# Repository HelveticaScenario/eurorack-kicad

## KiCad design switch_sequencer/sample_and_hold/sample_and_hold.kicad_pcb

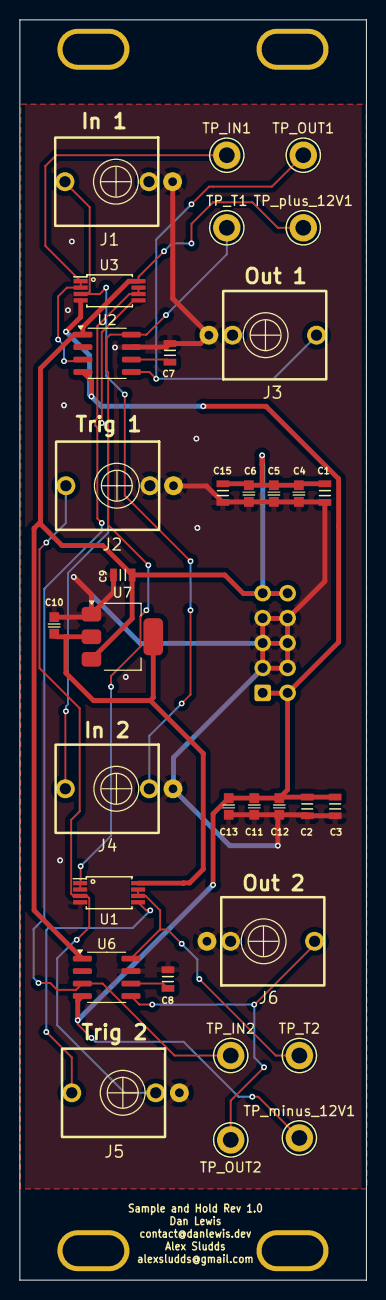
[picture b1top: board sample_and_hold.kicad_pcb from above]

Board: 2 copper layers, 35.3 x 128.5 mm, 38 parts (1 on the bottom side), 16 nets.

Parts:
C1, C2, C3, C15: 22uF_0603_16V; C_0805
C4, C5, C6, C11, C12, C13: 100nF_0603_16V; C_0603
C7, C8, C9: 0.1uF_0805_50V; C_0805
C10: 10uF_0603_10V; C_0603
H1, H2, H3, H4: MountingHole; Faceplate_Rail_Mount_Slot_Plated
J1, J2, J3, J4, J5, J6: 3.5mm_Mono_Switched_sm; EighthInch_PJ398SM
J7: Eurorack_Power_10pin_Shrouded; Pins_2x05_2.54mm_TH_EurorackPower_Shrouded
TP_IN1, TP_IN2: TestPoint; TestPoint_Keystone_5005-5009_Compact
TP_OUT1, TP_OUT2: TestPoint; TestPoint_Keystone_5005-5009_Compact
TP_T1, TP_T2: TestPoint; TestPoint_Keystone_5005-5009_Compact
TP_minus_12V1: TestPoint; TestPoint_Keystone_5005-5009_Compact
TP_plus_12V1: TestPoint; TestPoint_Keystone_5005-5009_Compact
U1, U3: TL072; TSSOP-8_4.4x3mm_Pitch0.65mm
U2, U6: LF398_SOIC8; SOIC-8_3.9x4.9mm_P1.27mm
U7: LD1117S50TR_SOT223; SOT-223-3_TabPin2

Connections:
5V: C10.1, U1.8 (V+), U7.2 (VO)
+12V: C1.1, C4.1, C5.1, C6.1, C9.1, C15.1, J7.9 (+12V), J7.10 (+12V), TP_plus_12V1.1, U2.1 (V^{+}), U3.8 (V+), U6.1 (V^{+}), U7.3 (VI)
-12VA: C2.2, C3.2, C11.2, C12.2, C13.2, J7.1 (-12V), J7.2 (-12V), TP_minus_12V1.1, U2.4 (V^{-}), U3.4 (V-), U6.4 (V^{-})
/out1: J3.1 (SIG), TP_OUT1.1, U2.5
/out2: J6.1 (SIG), TP_OUT2.1, U6.5
GND: C1.2, C2.1, C3.1, C4.2, C5.2, C6.2, C7.2, C8.2, C9.2, C10.2, C11.1, C12.1, C13.1, C15.2, J1.2 (SHEILD), J1.3 (SW), J2.2 (SHEILD), J2.3 (SW), J3.2 (SHEILD), J3.3 (SW), J4.2 (SHEILD), J5.2 (SHEILD), J6.2 (SHEILD), J6.3 (SW), J7.3 (GND), J7.4 (GND), J7.5 (GND), J7.6 (GND), J7.7 (GND), J7.8 (GND), U1.4 (V-), U2.7 (T), U6.7 (T), U7.1 (GND)
unnamed: J4.1 (SIG), U3.5 (+)
unnamed: J5.1 (SIG), U1.5 (+)
unnamed: TP_T1.1, U1.1, U1.2 (-), U2.8 (Hold)
unnamed: TP_T2.1, U1.6 (-), U1.7, U6.8 (Hold)
unnamed: C7.1, U2.6 (C_{h})
unnamed: TP_IN1.1, U2.3 (I), U3.1, U3.2 (-)
unnamed: TP_IN2.1, U3.6 (-), U3.7, U6.3 (I)
unnamed: C8.1, U6.6 (C_{h})
SIGNAL 1: J1.1 (SIG), J4.3 (SW), U3.3 (+)
TRIG 1: J2.1 (SIG), J5.3 (SW), U1.3 (+)

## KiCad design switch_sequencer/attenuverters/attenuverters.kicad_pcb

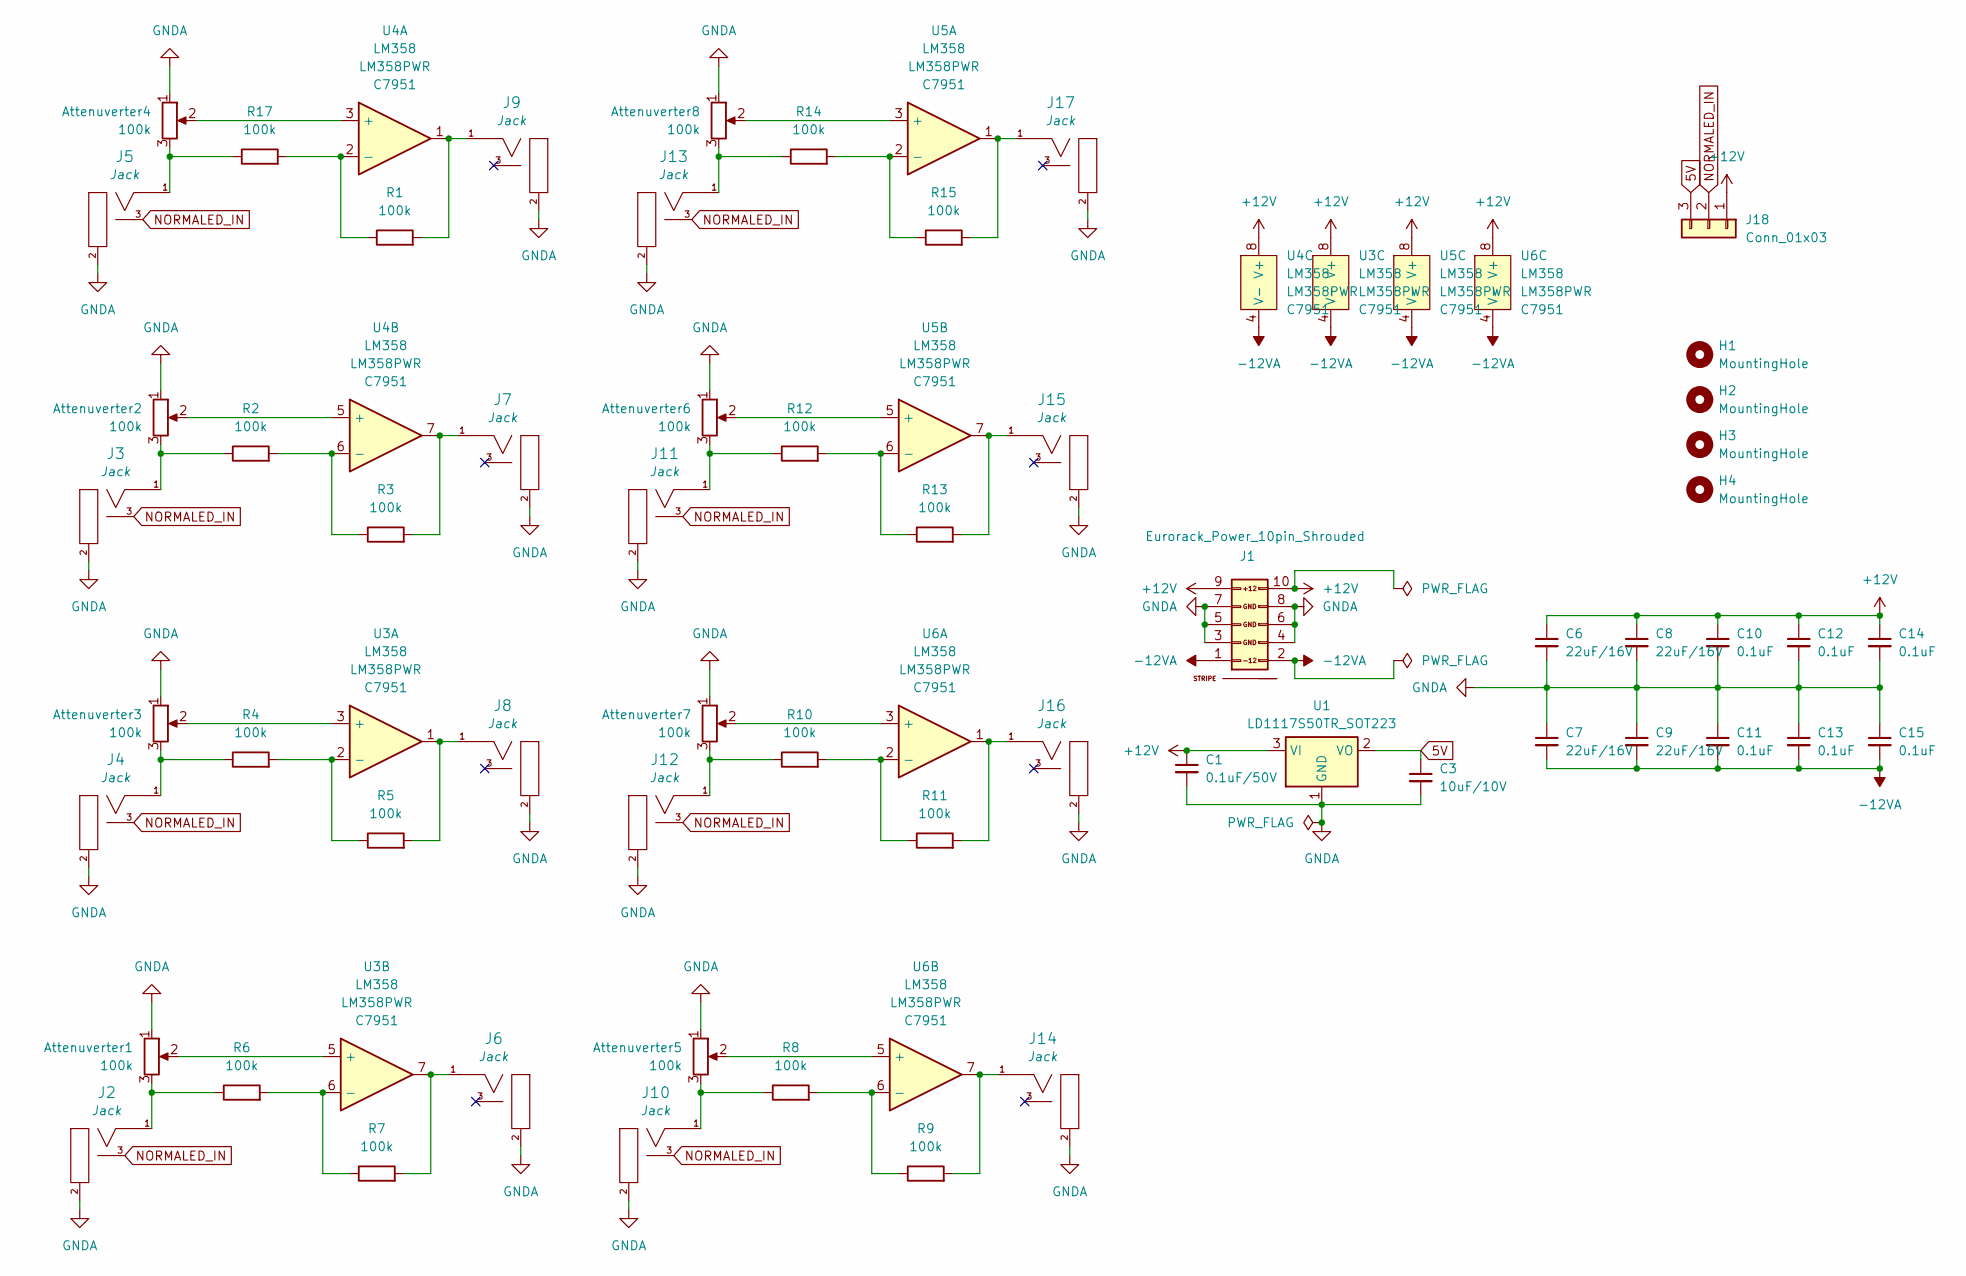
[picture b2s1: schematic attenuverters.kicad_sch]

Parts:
Attenuverter1, Attenuverter2, Attenuverter3, Attenuverter4, Attenuverter5, Attenuverter6, Attenuverter7, Attenuverter8: 100k; Alpha9mmPot
C1: 0.1uF_0805_50V; C_0805; Part Number GCJ21BL81H104KA01L
C3: 10uF_0603_10V; C_0603; Part Number GRM188R61A106KE69D; JLCPCB ID C19702
C6, C7, C8, C9: 22uF_0603_16V; C_0805; Part Number GRM219R61C226ME15K
C10, C11, C12, C13, C14, C15: 100nF_0603_16V; C_0603; Part Number 0603YC104KAT2A; JLCPCB ID C14663
H1, H2, H3, H4: MountingHole; Faceplate_Rail_Mount_Slot_Plated
J1: Eurorack_Power_10pin_Shrouded; Pins_2x05_2.54mm_TH_EurorackPower_Shrouded; Part Number 61201021621
J2, J3, J4, J5, J6, J7, J8, J9, J10, J11, J12, J13, J14, J15, J16, J17: 3.5mm_Mono_Switched_sm; EighthInch_PJ398SM; Part Number WQP-WQP518MA
J18: Conn_01x03; Pins_1x03_2.54mm_TH; Part Number 1-0301FBV0T
R1, R2, R3, R4, R5, R6, R7, R8, R9, R10, R11, R12, R13, R14, R15, R17: 100k_0402; R_0402; Part Number RC0402FR-07100KL; JLCPCB ID C60491
U1: LD1117S50TR_SOT223; SOT-223-3_TabPin2
U3, U4, U5, U6: LM358; TSSOP-8_4.4x3mm_Pitch0.65mm; Part Number LM358PWR; JLCPCB ID C7951

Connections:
5V: C3.1, J18.3, U1.2 (VO)
+12V: C1.1, C6.1, C8.1, C10.1, C12.1, C14.1, J1.9 (+12V), J1.10 (+12V), J18.1, U1.3 (VI), U3.8 (V+), U4.8 (V+), U5.8 (V+), U6.8 (V+)
-12VA: C7.2, C9.2, C11.2, C13.2, C15.2, J1.1 (-12V), J1.2 (-12V), U3.4 (V-), U4.4 (V-), U5.4 (V-), U6.4 (V-)
GNDA: Attenuverter1.1, Attenuverter2.1, Attenuverter3.1, Attenuverter4.1, Attenuverter5.1, Attenuverter6.1, Attenuverter7.1, Attenuverter8.1, C1.2, C3.2, C6.2, C7.1, C8.2, C9.1, C10.2, C11.1, C12.2, C13.1, C14.2, C15.1, J1.3 (GND), J1.4 (GND), J1.5 (GND), J1.6 (GND), J1.7 (GND), J1.8 (GND), J2.2 (SHEILD), J3.2 (SHEILD), J4.2 (SHEILD), J5.2 (SHEILD), J6.2 (SHEILD), J7.2 (SHEILD), J8.2 (SHEILD), J9.2 (SHEILD), J10.2 (SHEILD), J11.2 (SHEILD), J12.2 (SHEILD), J13.2 (SHEILD), J14.2 (SHEILD), J15.2 (SHEILD), J16.2 (SHEILD), J17.2 (SHEILD), U1.1 (GND)
NORMALED_IN: J2.3 (SW), J3.3 (SW), J4.3 (SW), J5.3 (SW), J10.3 (SW), J11.3 (SW), J12.3 (SW), J13.3 (SW), J18.2
unnamed: Attenuverter1.3, J2.1 (SIG), R6.1
unnamed: Attenuverter2.3, J3.1 (SIG), R2.1
unnamed: Attenuverter3.3, J4.1 (SIG), R4.1
unnamed: Attenuverter4.3, J5.1 (SIG), R17.1
unnamed: J6.1 (SIG), R7.2, U3.7
unnamed: J7.1 (SIG), R3.2, U4.7
unnamed: J8.1 (SIG), R5.2, U3.1
unnamed: J9.1 (SIG), R1.2, U4.1
unnamed: Attenuverter5.3, J10.1 (SIG), R8.1
unnamed: Attenuverter6.3, J11.1 (SIG), R12.1
unnamed: Attenuverter7.3, J12.1 (SIG), R10.1
unnamed: Attenuverter8.3, J13.1 (SIG), R14.1
unnamed: J14.1 (SIG), R9.2, U6.7
unnamed: J15.1 (SIG), R13.2, U5.7
unnamed: J16.1 (SIG), R11.2, U6.1
unnamed: J17.1 (SIG), R15.2, U5.1
unnamed: Attenuverter3.2, U3.3 (+)
unnamed: R4.2, R5.1, U3.2 (-)
unnamed: Attenuverter1.2, U3.5 (+)
unnamed: R6.2, R7.1, U3.6 (-)
unnamed: Attenuverter4.2, U4.3 (+)
unnamed: R1.1, R17.2, U4.2 (-)
unnamed: Attenuverter2.2, U4.5 (+)
unnamed: R2.2, R3.1, U4.6 (-)
unnamed: Attenuverter8.2, U5.3 (+)
unnamed: R14.2, R15.1, U5.2 (-)
unnamed: Attenuverter6.2, U5.5 (+)
unnamed: R12.2, R13.1, U5.6 (-)
unnamed: Attenuverter7.2, U6.3 (+)
unnamed: R10.2, R11.1, U6.2 (-)
unnamed: Attenuverter5.2, U6.5 (+)
unnamed: R8.2, R9.1, U6.6 (-)

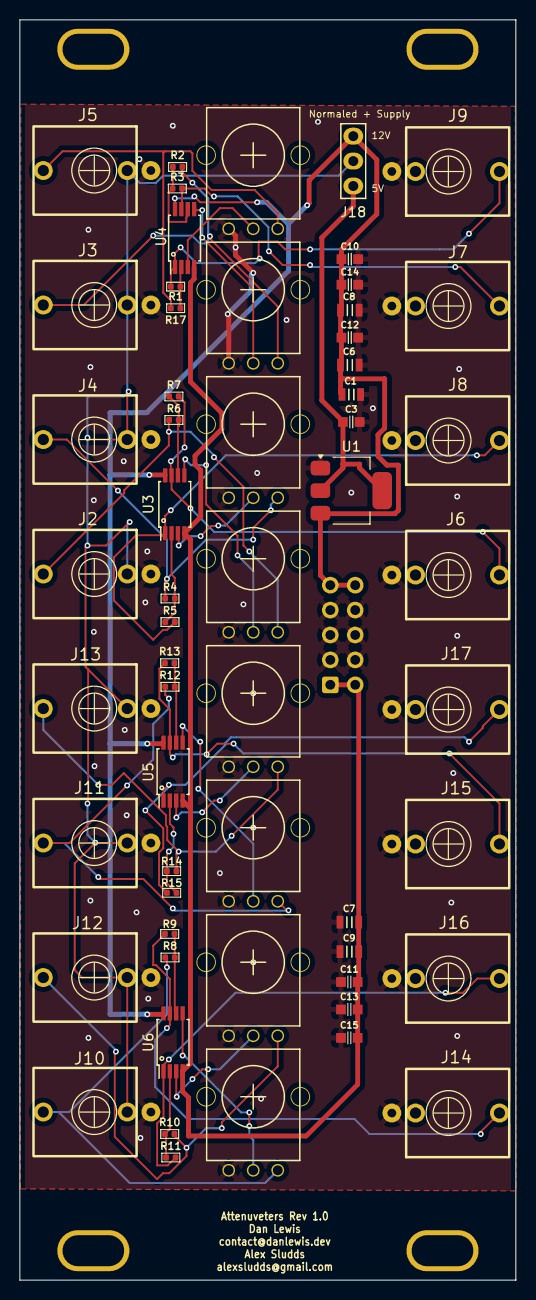
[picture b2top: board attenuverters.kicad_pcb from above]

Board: 2 copper layers, 50.6 x 128.5 mm, 63 parts (1 on the bottom side), 37 nets.

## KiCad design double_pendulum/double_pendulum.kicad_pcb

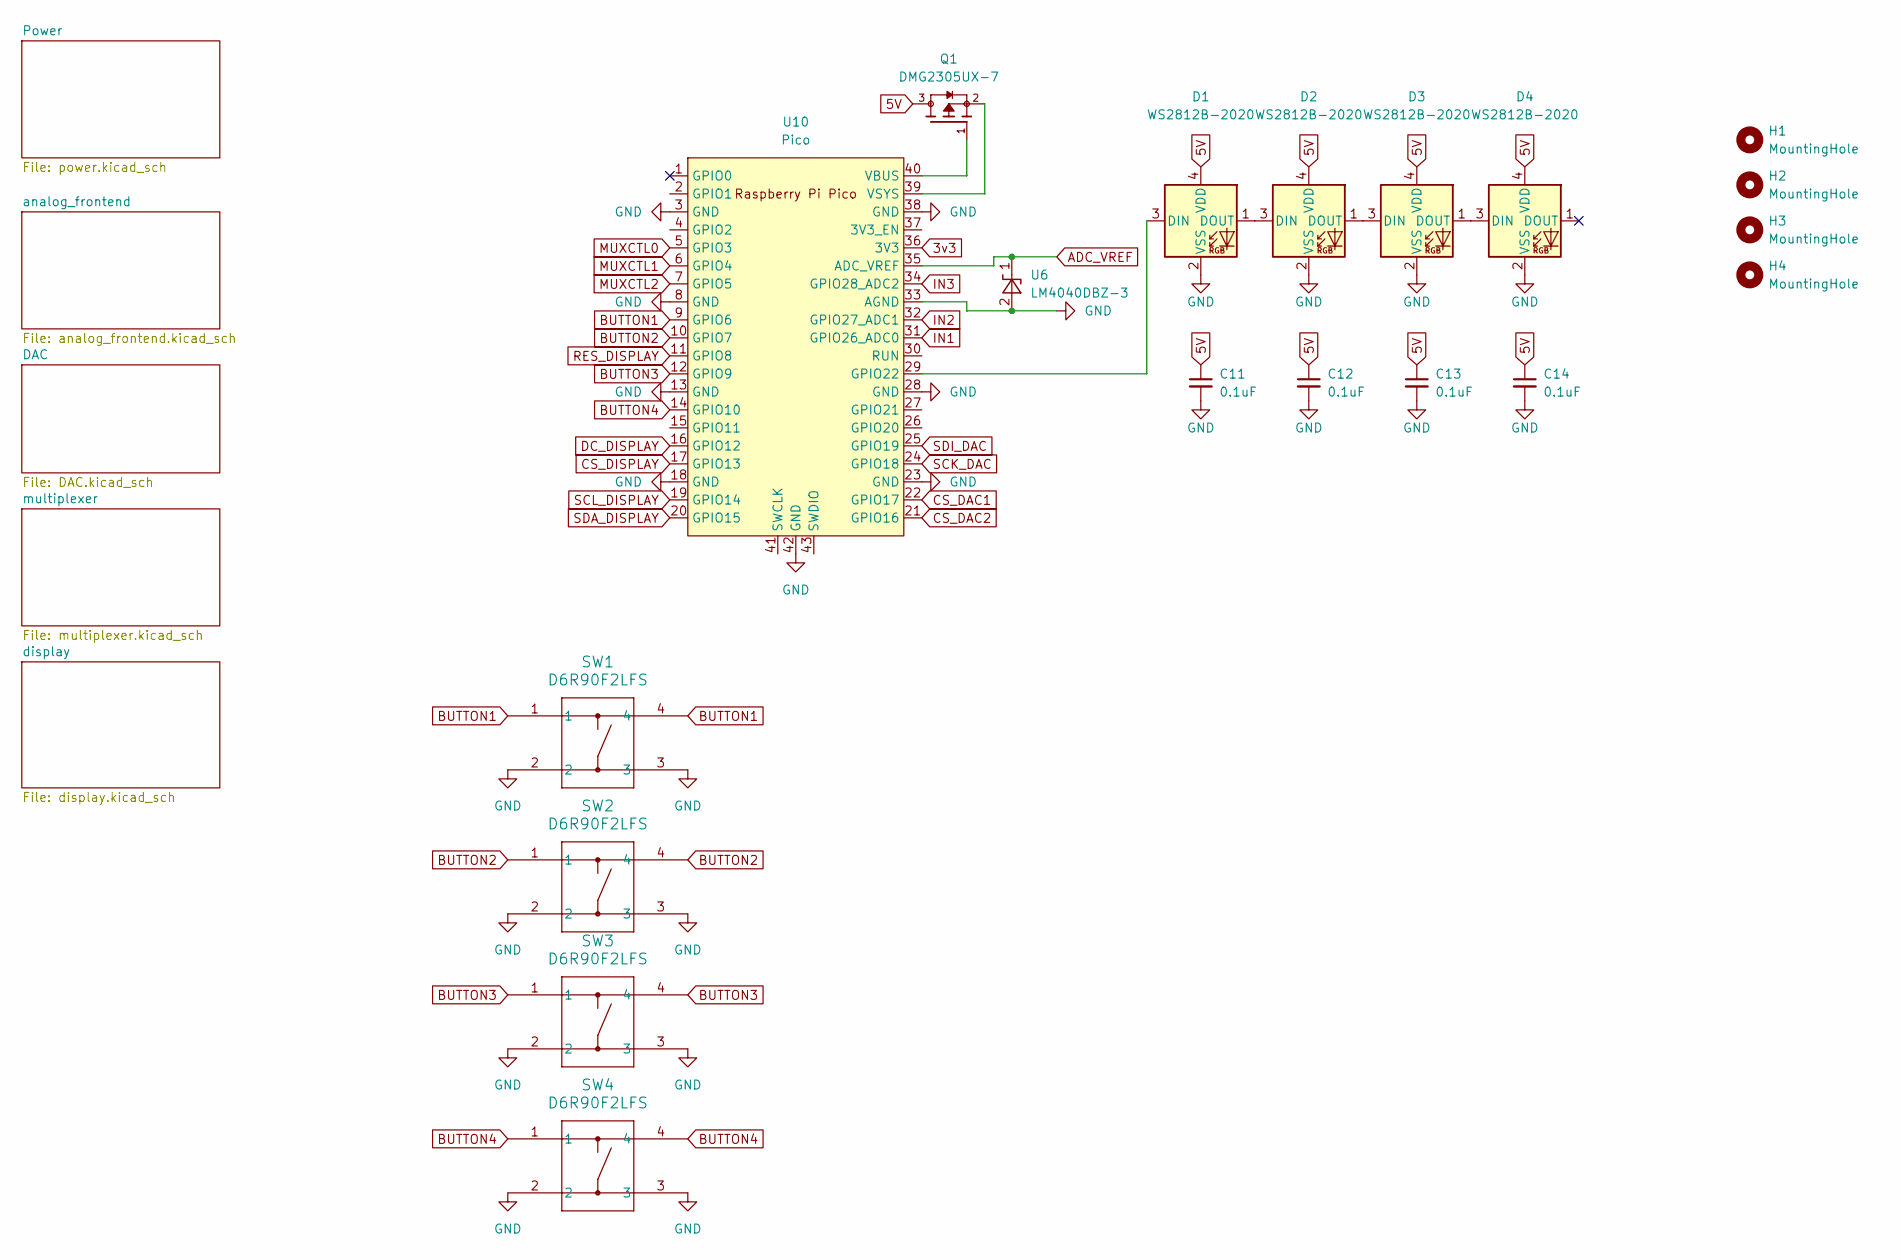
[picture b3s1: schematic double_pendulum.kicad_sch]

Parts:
C11, C12, C13, C14: 100nF_0402_16V; C_0402; Part Number GCM155R71C104KA55D; JLCPCB ID C1525
D1, D2, D3, D4: WS2812B-2020; LED_WS2812B-2020_PLCC4_2.0x2.0mm
H1, H2, H3, H4: MountingHole; Faceplate_Rail_Mount_Slot_Plated
Q1: DMG2305UX-7; SOT91P240X110-3N_DMG2305UX-7; PARTREV 09/2018
SW1, SW2, SW3, SW4: D6R90F2LFS; D6R90_CNK
U6: LM4040DBZ-3; SOT-23
U10: Pico; RPi_Pico_SMD_TH

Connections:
3v3: U10.36 (3V3); also elsewhere on the board
5V: C11.1, C12.1, C13.1, C14.1, D1.4 (VDD), D2.4 (VDD), D3.4 (VDD), D4.4 (VDD), Q1.3; also elsewhere on the board
ADC_VREF: U6.1 (K), U10.35 (ADC_VREF)
BUTTON1: SW1.1, SW1.4, U10.9 (GPIO6)
BUTTON2: SW2.1, SW2.4, U10.10 (GPIO7)
BUTTON3: SW3.1, SW3.4, U10.12 (GPIO9)
BUTTON4: SW4.1, SW4.4, U10.14 (GPIO10)
CS_DAC1: U10.22 (GPIO17); also elsewhere on the board
CS_DAC2: U10.21 (GPIO16); also elsewhere on the board
CS_DISPLAY: U10.17 (GPIO13); also elsewhere on the board
DC_DISPLAY: U10.16 (GPIO12); also elsewhere on the board
GND: C11.2, C12.2, C13.2, C14.2, D1.2 (VSS), D2.2 (VSS), D3.2 (VSS), D4.2 (VSS), SW1.2, SW1.3, SW2.2, SW2.3, SW3.2, SW3.3, SW4.2, SW4.3, U6.2 (A), U10.3 (GND), U10.8 (GND), U10.13 (GND), U10.18 (GND), U10.23 (GND), U10.28 (GND), U10.33 (AGND), U10.38 (GND), U10.42 (GND); also elsewhere on the board
IN1: U10.31 (GPIO26_ADC0); also elsewhere on the board
IN2: U10.32 (GPIO27_ADC1); also elsewhere on the board
IN3: U10.34 (GPIO28_ADC2); also elsewhere on the board
MUXCTL0: U10.5 (GPIO3); also elsewhere on the board
MUXCTL1: U10.6 (GPIO4); also elsewhere on the board
MUXCTL2: U10.7 (GPIO5); also elsewhere on the board
unnamed: D1.3 (DIN), U10.29 (GPIO22)
unnamed: D1.1 (DOUT), D2.3 (DIN)
unnamed: D2.1 (DOUT), D3.3 (DIN)
unnamed: D3.1 (DOUT), D4.3 (DIN)
unnamed: Q1.1, U10.40 (VBUS)
unnamed: Q1.2, U10.39 (VSYS)
RES_DISPLAY: U10.11 (GPIO8); also elsewhere on the board
SCK_DAC: U10.24 (GPIO18); also elsewhere on the board
SCL_DISPLAY: U10.19 (GPIO14); also elsewhere on the board
SDA_DISPLAY: U10.20 (GPIO15); also elsewhere on the board
SDI_DAC: U10.25 (GPIO19); also elsewhere on the board

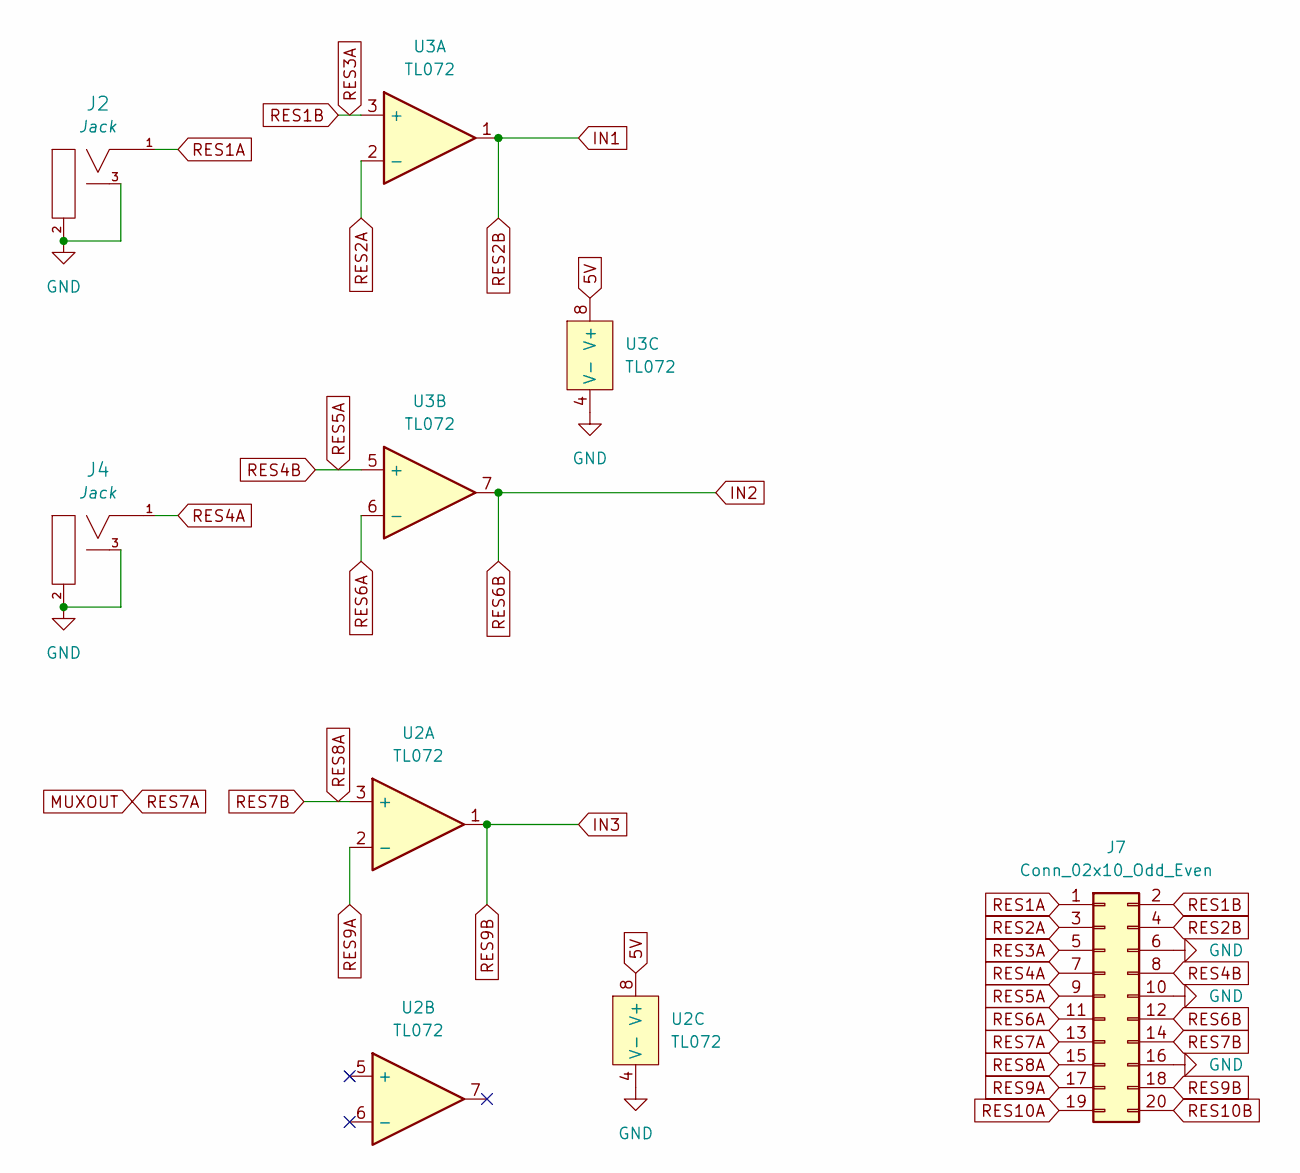
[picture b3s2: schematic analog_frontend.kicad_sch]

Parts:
J2, J4: 3.5mm_Mono_Switched_sm; EighthInch_PJ398SM; Part Number WQP-WQP518MA
J7: Conn_02x10_Odd_Even; DIP-20_W7.62mm_Socket
U2, U3: TL072; TSSOP-8_4.4x3mm_Pitch0.65mm; JLCPCB ID C90748

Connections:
5V: U2.8 (V+), U3.8 (V+); also elsewhere on the board
GND: J2.2 (SHEILD), J2.3 (SW), J4.2 (SHEILD), J4.3 (SW), J7.6, J7.10, J7.16, U2.4 (V-), U3.4 (V-); also elsewhere on the board
IN1: J7.4, U3.1; also elsewhere on the board
IN2: J7.12, U3.7; also elsewhere on the board
IN3: J7.18, U2.1; also elsewhere on the board
MUXOUT: J7.13; also elsewhere on the board
RES1A: J2.1 (SIG), J7.1
RES1B: J7.2, J7.5, U3.3 (+)
RES2A: J7.3, U3.2 (-)
RES4A: J4.1 (SIG), J7.7
RES4B: J7.8, J7.9, U3.5 (+)
RES6A: J7.11, U3.6 (-)
RES7B: J7.14, J7.15, U2.3 (+)
RES9A: J7.17, U2.2 (-)
RES10A: J7.19
RES10B: J7.20

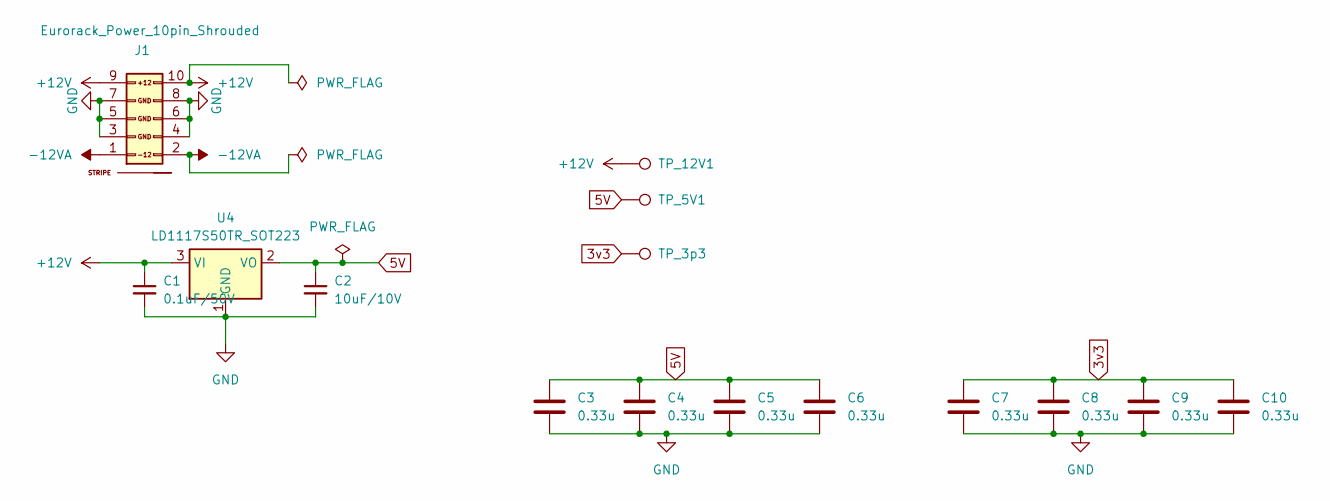
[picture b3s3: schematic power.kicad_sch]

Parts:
C1: 0.1uF_0805_50V; C_0805_2012Metric; Part Number GCJ21BL81H104KA01L
C2: 10uF_0603_10V; C_0805_2012Metric; Part Number GRM188R61A106KE69D; JLCPCB ID C19702
C3, C4, C5, C6, C7, C8, C9, C10: 0.33u; C_0805_2012Metric
J1: Eurorack_Power_10pin_Shrouded; Pins_2x05_2.54mm_TH_EurorackPower_Shrouded; Part Number 61201021621
TP_3p3, TP_5V1, TP_12V1: TestPoint; TestPoint_Keystone_5005-5009_Compact
U4: LD1117S50TR_SOT223; SOT-223-3_TabPin2

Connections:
3v3: C7.1, C8.1, C9.1, C10.1, TP_3p3.1; also elsewhere on the board
5V: C2.1, C3.1, C4.1, C5.1, C6.1, TP_5V1.1, U4.2 (VO); also elsewhere on the board
+12V: C1.1, J1.9 (+12V), J1.10 (+12V), TP_12V1.1, U4.3 (VI)
-12VA: J1.1 (-12V), J1.2 (-12V)
GND: C1.2, C2.2, C3.2, C4.2, C5.2, C6.2, C7.2, C8.2, C9.2, C10.2, J1.3 (GND), J1.4 (GND), J1.5 (GND), J1.6 (GND), J1.7 (GND), J1.8 (GND), U4.1 (GND); also elsewhere on the board

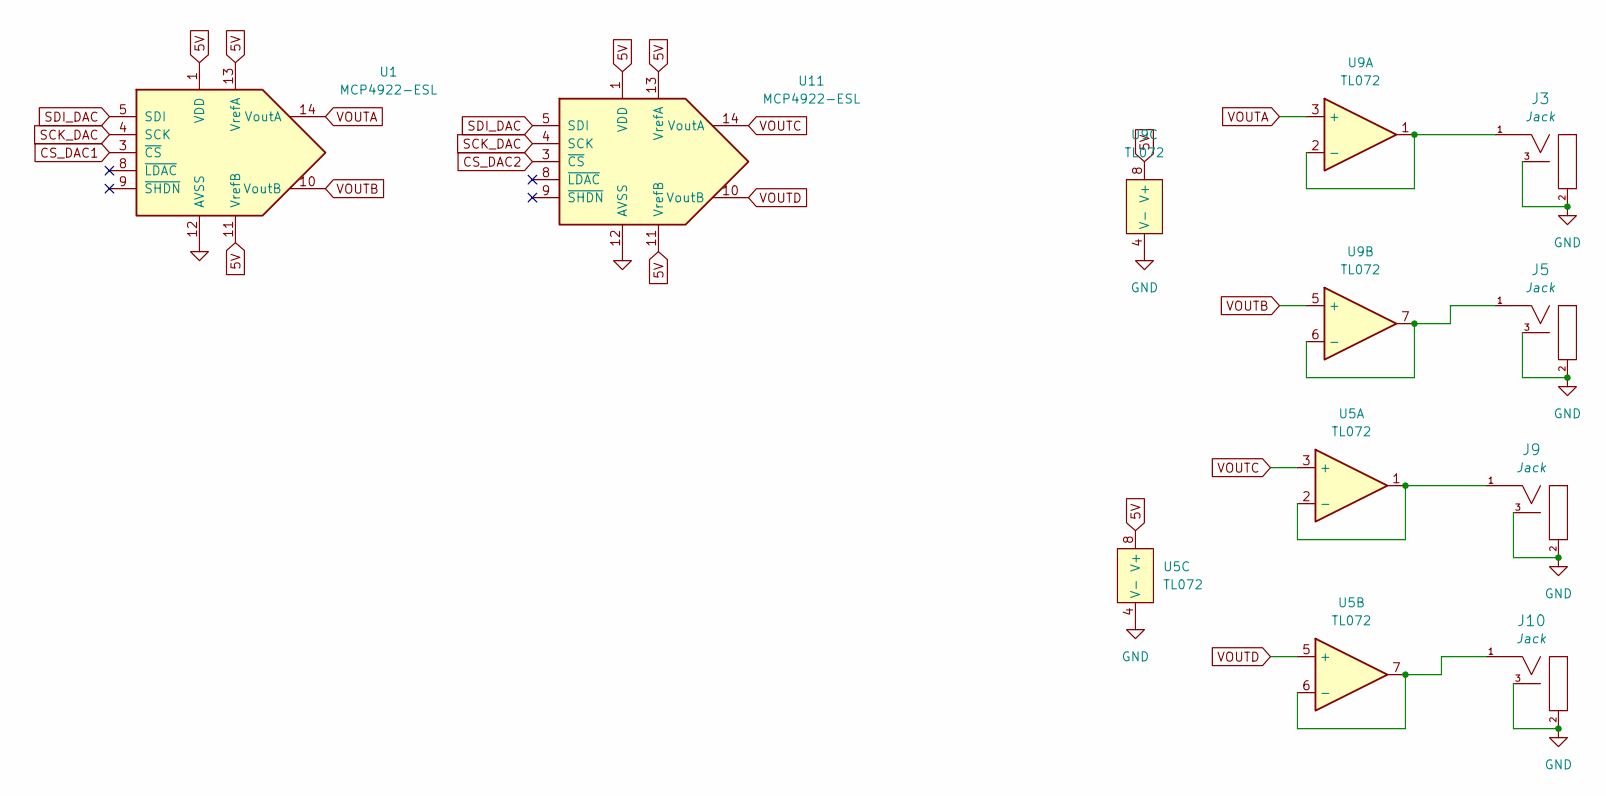
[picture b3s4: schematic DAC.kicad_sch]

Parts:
J3, J5, J9, J10: 3.5mm_Mono_Switched_sm; EighthInch_PJ398SM; Part Number WQP-WQP518MA
U1, U11: MCP4922-ESL; SOIC-14_3.9x8.65mm_Pitch1.27mm
U5, U9: TL072; TSSOP-8_4.4x3mm_Pitch0.65mm; JLCPCB ID C90748

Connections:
5V: U1.1 (VDD), U1.11 (VrefB), U1.13 (VrefA), U5.8 (V+), U9.8 (V+), U11.1 (VDD), U11.11 (VrefB), U11.13 (VrefA); also elsewhere on the board
CS_DAC1: U1.3 (~CS); also elsewhere on the board
CS_DAC2: U11.3 (~CS); also elsewhere on the board
GND: J3.2 (SHEILD), J3.3 (SW), J5.2 (SHEILD), J5.3 (SW), J9.2 (SHEILD), J9.3 (SW), J10.2 (SHEILD), J10.3 (SW), U1.12 (AVSS), U5.4 (V-), U9.4 (V-), U11.12 (AVSS); also elsewhere on the board
unnamed: J3.1 (SIG), U9.1, U9.2 (-)
unnamed: J5.1 (SIG), U9.6 (-), U9.7
unnamed: J9.1 (SIG), U5.1, U5.2 (-)
unnamed: J10.1 (SIG), U5.6 (-), U5.7
SCK_DAC: U1.4 (SCK), U11.4 (SCK); also elsewhere on the board
SDI_DAC: U1.5 (SDI), U11.5 (SDI); also elsewhere on the board
VOUTA: U1.14 (VoutA), U9.3 (+)
VOUTB: U1.10 (VoutB), U9.5 (+)
VOUTC: U5.3 (+), U11.14 (VoutA)
VOUTD: U5.5 (+), U11.10 (VoutB)

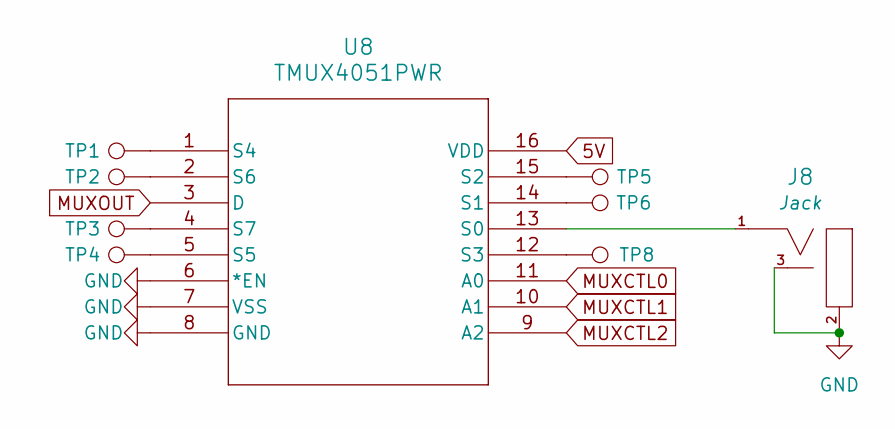
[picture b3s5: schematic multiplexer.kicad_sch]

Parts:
J8: 3.5mm_Mono_Switched_sm; EighthInch_PJ398SM; Part Number WQP-WQP518MA
TP1, TP2, TP3, TP4, TP5, TP6, TP8: TestPoint; TestPoint_Keystone_5005-5009_Compact
U8: TMUX4051PWR; TSSOP16_PW_TEX

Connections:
5V: U8.16 (VDD); also elsewhere on the board
GND: J8.2 (SHEILD), J8.3 (SW), U8.6 (*EN), U8.7 (VSS), U8.8 (GND); also elsewhere on the board
MUXCTL0: U8.11 (A0); also elsewhere on the board
MUXCTL1: U8.10 (A1); also elsewhere on the board
MUXCTL2: U8.9 (A2); also elsewhere on the board
MUXOUT: U8.3 (D); also elsewhere on the board
unnamed: J8.1 (SIG), U8.13 (S0)
unnamed: TP6.1, U8.14 (S1)
unnamed: TP5.1, U8.15 (S2)
unnamed: TP8.1, U8.12 (S3)
unnamed: TP1.1, U8.1 (S4)
unnamed: TP4.1, U8.5 (S5)
unnamed: TP2.1, U8.2 (S6)
unnamed: TP3.1, U8.4 (S7)

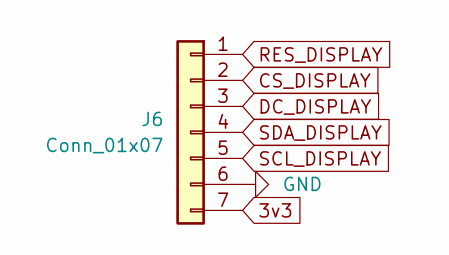
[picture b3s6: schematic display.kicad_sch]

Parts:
J6: Conn_01x07; JST_VH_B7P-VH_1x07_P3.96mm_Vertical

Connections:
3v3: J6.7; also elsewhere on the board
CS_DISPLAY: J6.2; also elsewhere on the board
DC_DISPLAY: J6.3; also elsewhere on the board
GND: J6.6; also elsewhere on the board
RES_DISPLAY: J6.1; also elsewhere on the board
SCL_DISPLAY: J6.5; also elsewhere on the board
SDA_DISPLAY: J6.4; also elsewhere on the board

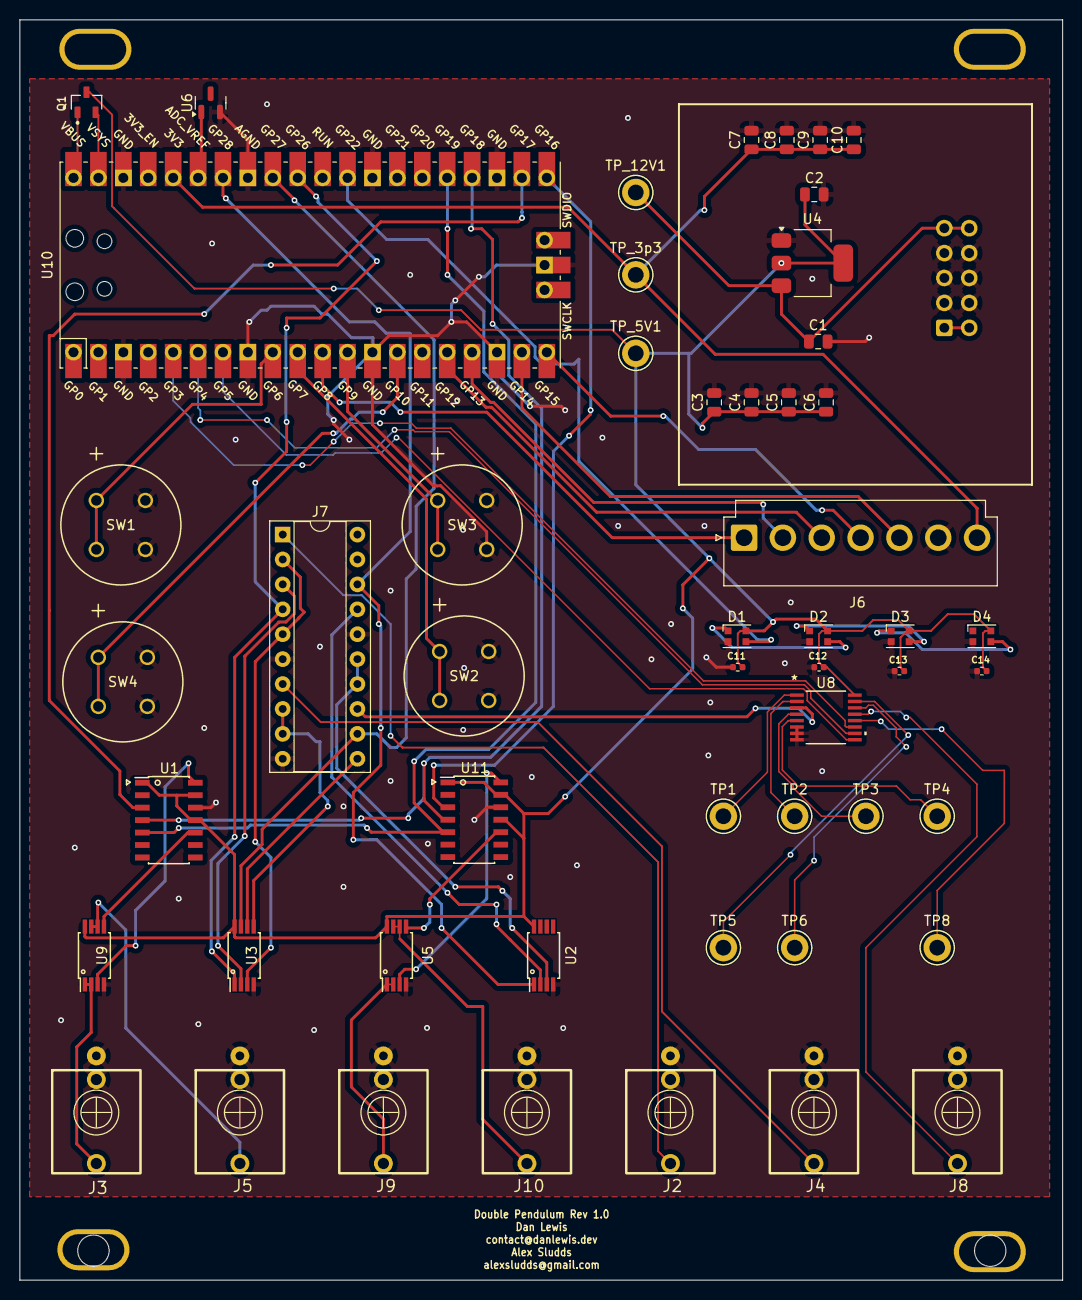
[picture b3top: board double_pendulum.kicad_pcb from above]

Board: 2 copper layers, 106.3 x 128.5 mm, 57 parts (1 on the bottom side), 56 nets.

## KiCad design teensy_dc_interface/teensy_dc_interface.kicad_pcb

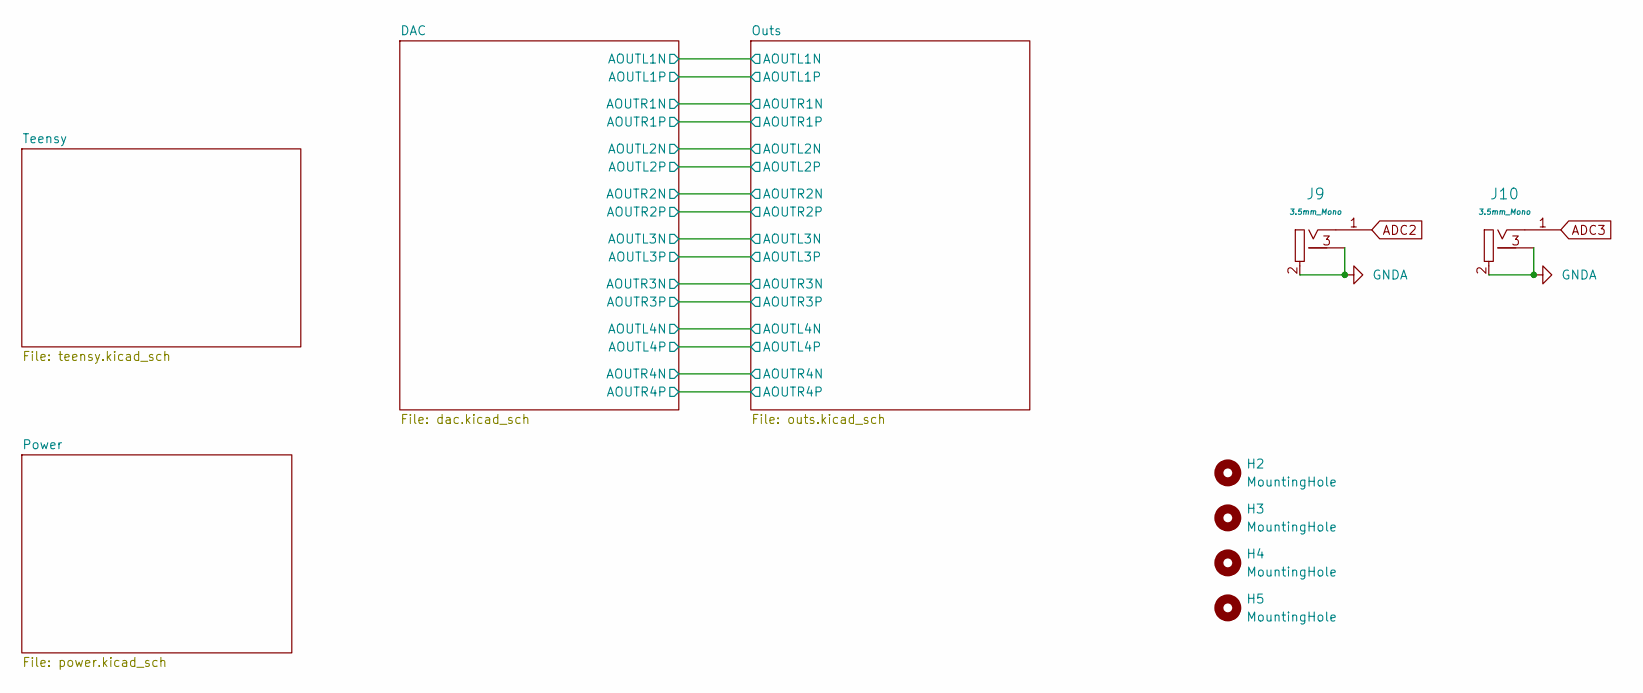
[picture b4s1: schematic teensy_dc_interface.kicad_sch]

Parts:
H2, H3, H4, H5: MountingHole; Faceplate_Rail_Mount_Slot_Plated
J9, J10: 3.5mm_Mono_Switched_SymSmall_0.05; EighthInch_PJ398SM; Part Number WQP-WQP518MA

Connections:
ADC2: J9.1 (SIG); also elsewhere on the board
ADC3: J10.1 (SIG); also elsewhere on the board
AVSS: J9.2 (SHEILD), J9.3 (SW), J10.2 (SHEILD), J10.3 (SW); also elsewhere on the board
